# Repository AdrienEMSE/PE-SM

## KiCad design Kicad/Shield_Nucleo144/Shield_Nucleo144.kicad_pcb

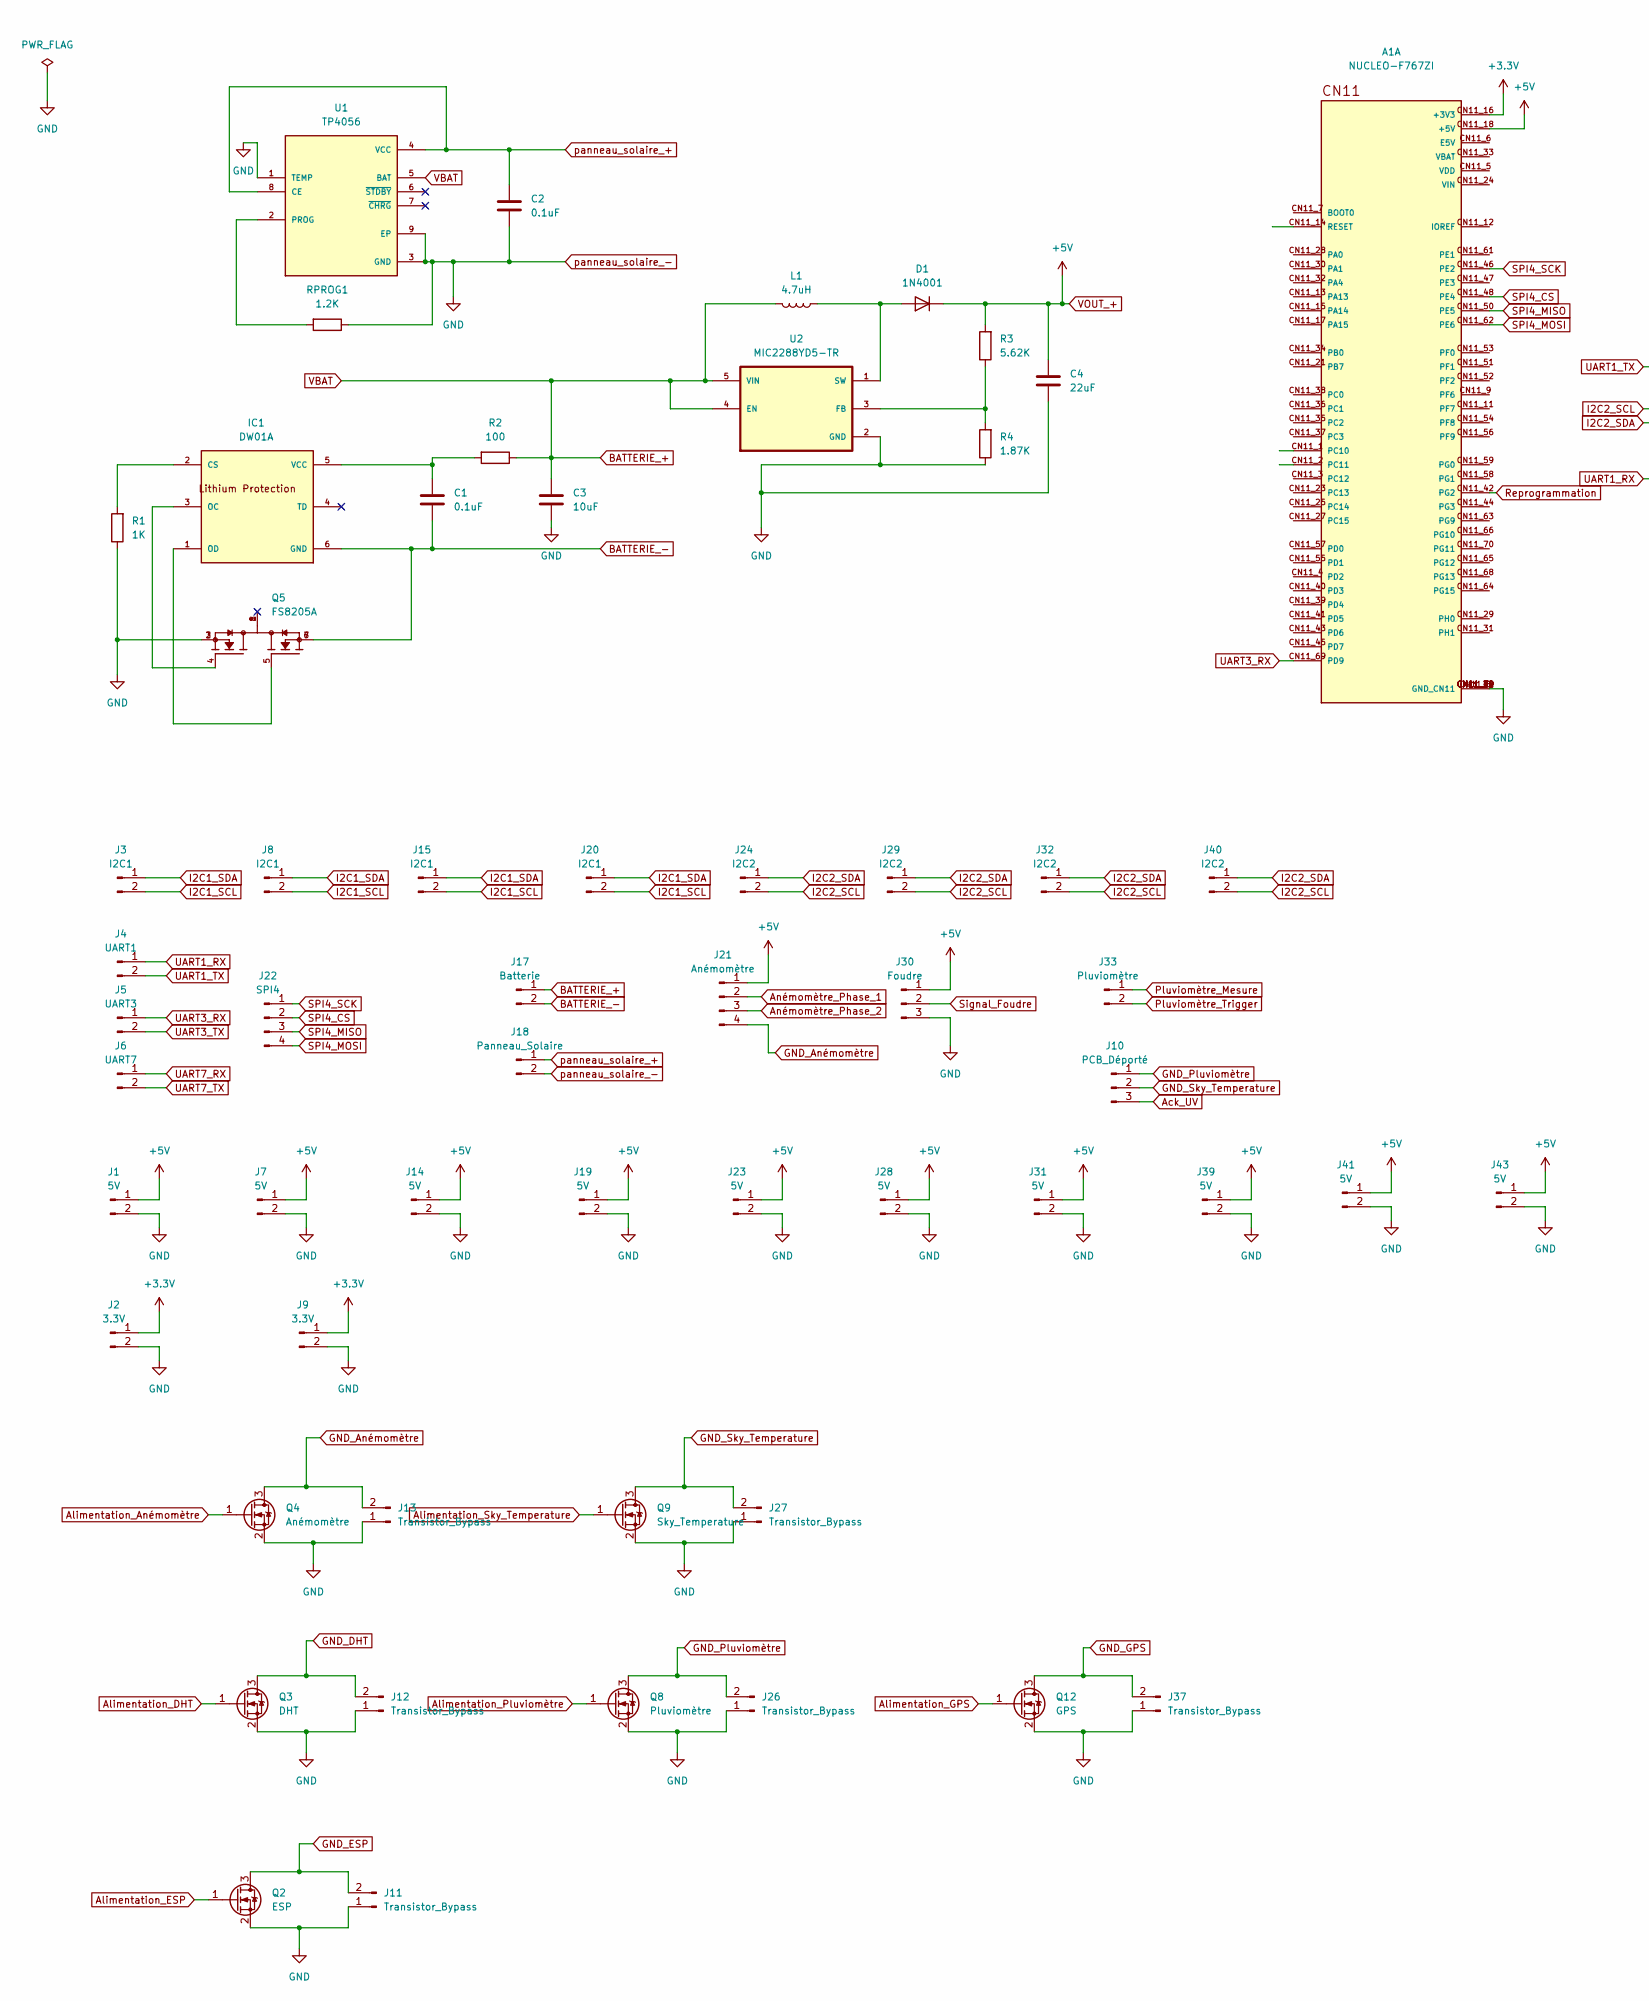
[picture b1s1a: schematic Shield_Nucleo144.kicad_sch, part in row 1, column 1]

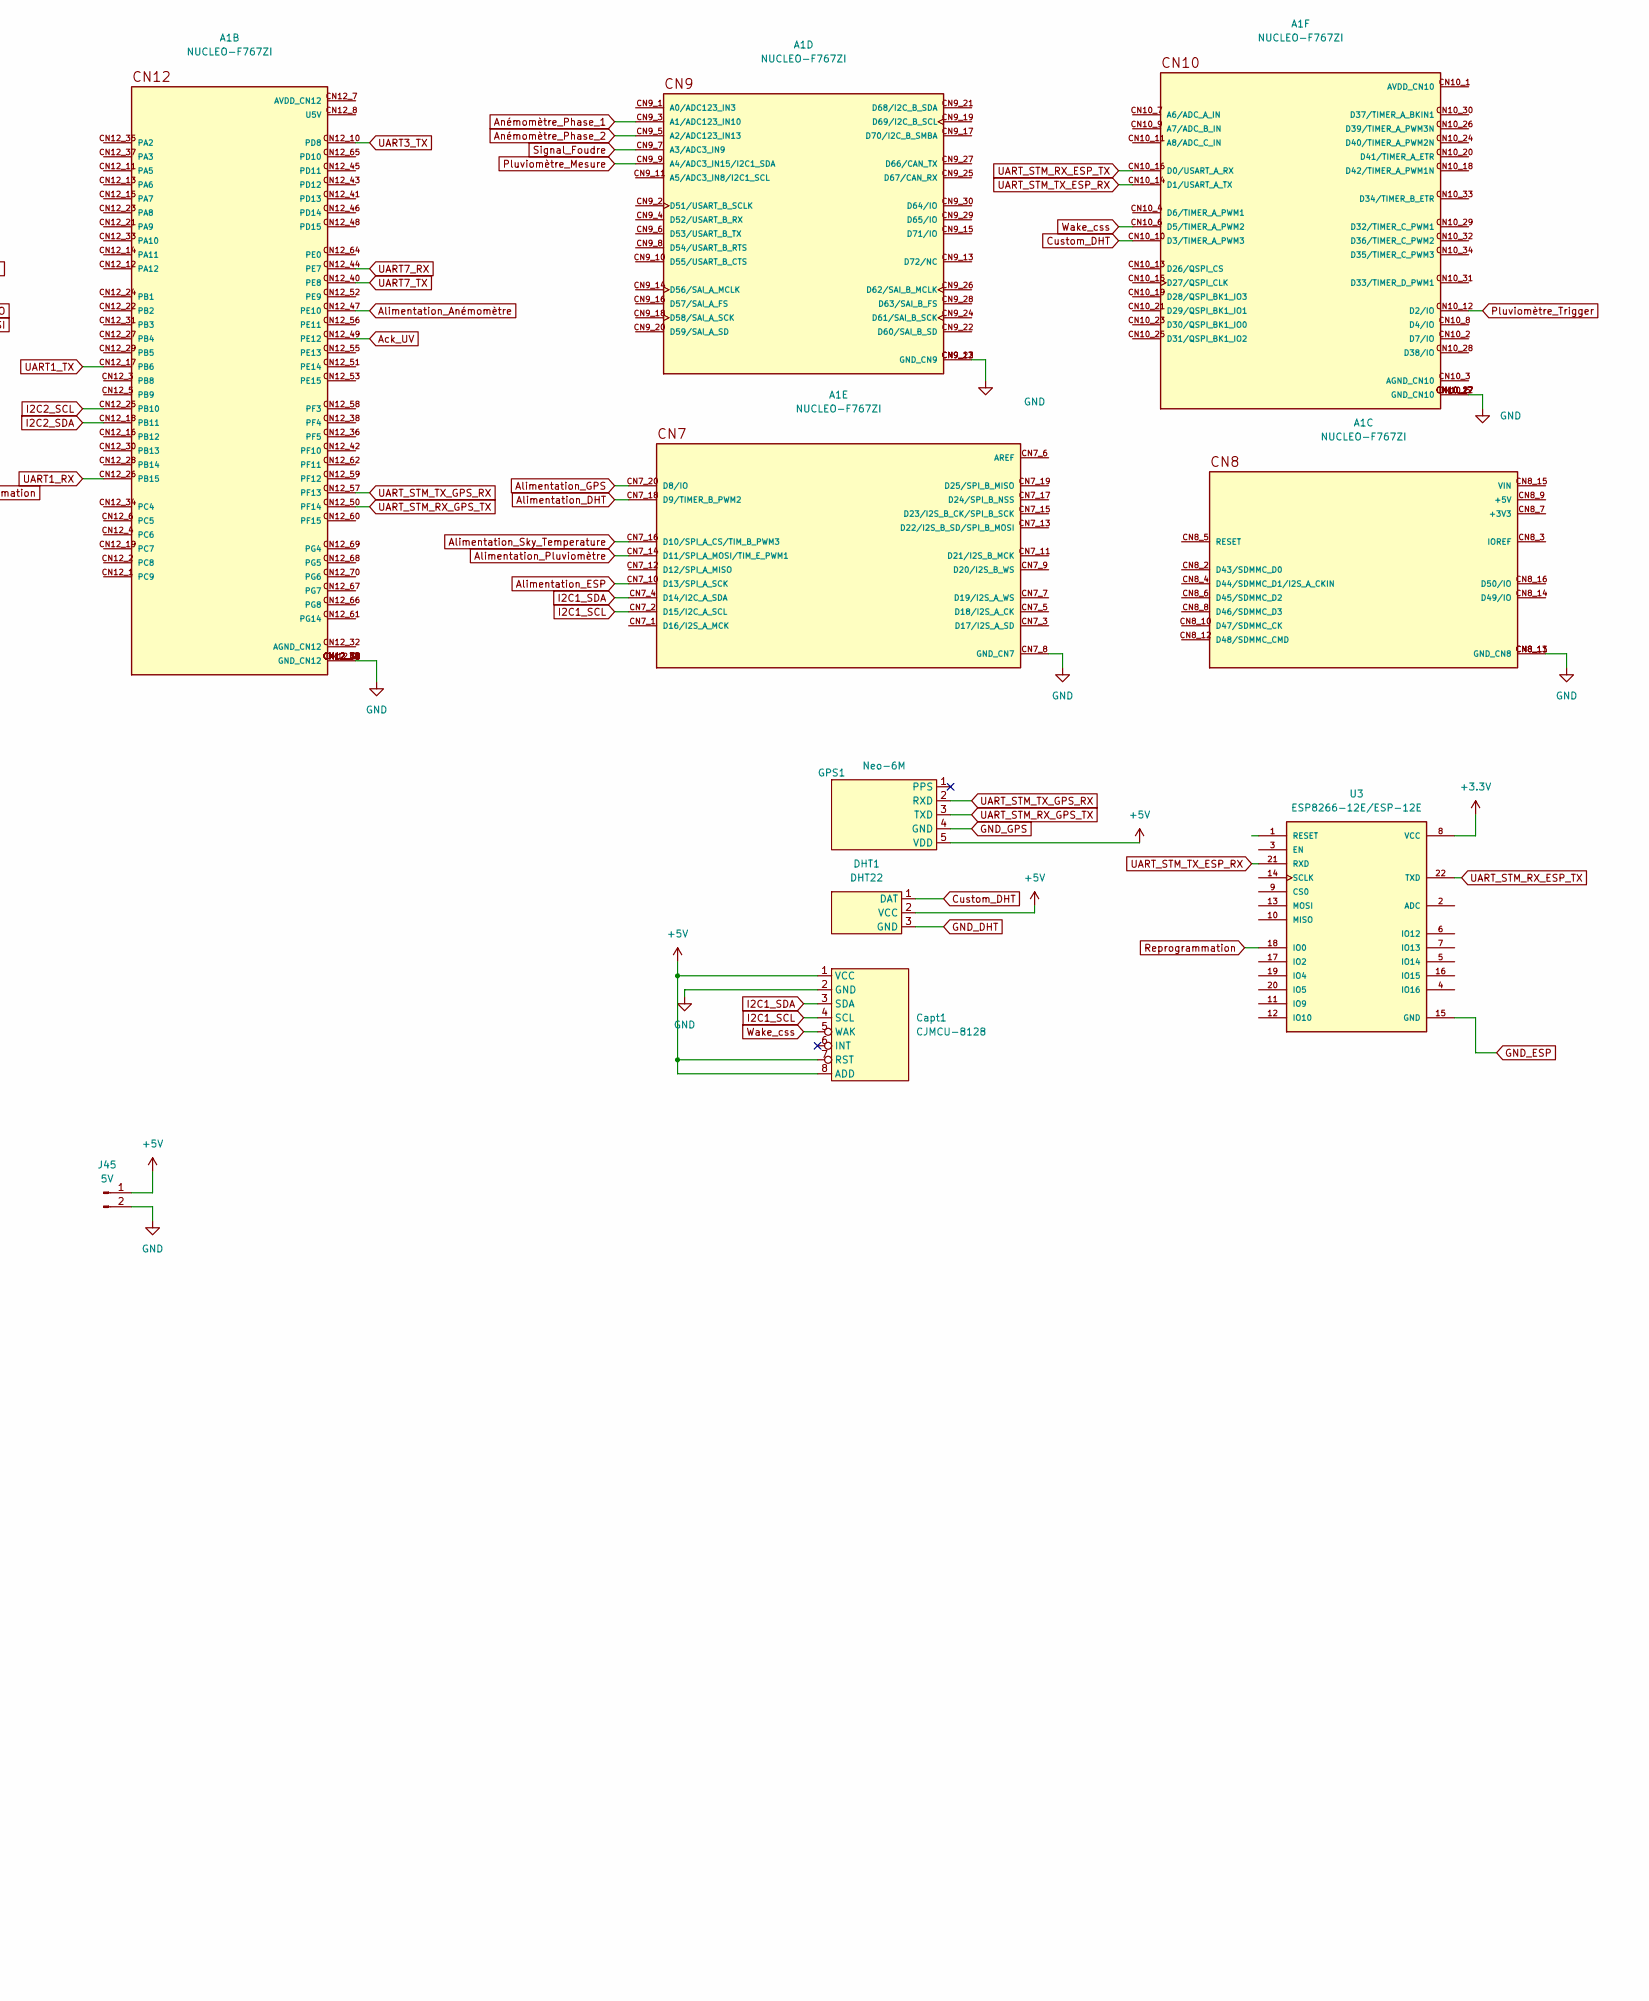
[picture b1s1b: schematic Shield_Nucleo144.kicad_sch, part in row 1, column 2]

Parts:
A1: NUCLEO-F767ZI; ST_NUCLEO-F767ZI; PARTREV 7
C1, C2: 0.1uF; C_0603_1608Metric
C3: 10uF; C_0603_1608Metric
C4: 22uF; C_0805_2012Metric
Capt1: CJMCU-8128; AQHT
D1: 1N4001; D_SOD-123
DHT1: DHT22; DHT
GPS1: Neo-6M; GPS
IC1: DW01A; SOT-23-6; MPN DW01A; LCSC C351410
J1, J7, J14, J19, J23, J28, J31, J39, J41, J43, J45: 5V; JST_EH_B2B-EH-A_1x02_P2.50mm_Vertical
J2, J9: 3.3V; JST_EH_B2B-EH-A_1x02_P2.50mm_Vertical
J3, J8, J15, J20: I2C1; JST_EH_B2B-EH-A_1x02_P2.50mm_Vertical
J4: UART1; JST_EH_B2B-EH-A_1x02_P2.50mm_Vertical
J5: UART3; JST_EH_B2B-EH-A_1x02_P2.50mm_Vertical
J6: UART7; JST_EH_B2B-EH-A_1x02_P2.50mm_Vertical
J10: PCB_Déporté; JST_EH_B3B-EH-A_1x03_P2.50mm_Vertical
J11, J12, J13, J26, J27, J37: Transistor_Bypass; PinHeader_1x02_P2.54mm_Vertical
J17: Batterie; JST_EH_B2B-EH-A_1x02_P2.50mm_Vertical
J18: Panneau_Solaire; JST_EH_B2B-EH-A_1x02_P2.50mm_Vertical
J21: Anémomètre; JST_EH_B4B-EH-A_1x04_P2.50mm_Vertical
J22: SPI4; JST_EH_B4B-EH-A_1x04_P2.50mm_Vertical
J24, J29, J32, J40: I2C2; JST_EH_B2B-EH-A_1x02_P2.50mm_Vertical
J30: Foudre; JST_EH_B3B-EH-A_1x03_P2.50mm_Vertical
J33: Pluviomètre; JST_EH_B2B-EH-A_1x02_P2.50mm_Vertical
L1: 4.7uH; L_Vishay_IHLP-2525
Q2: ESP; SOT-23
Q3: DHT; SOT-23
Q4: Anémomètre; SOT-23
Q5: FS8205A; SOP65P640X120-8N; PARTREV 1.7
Q8: Pluviomètre; SOT-23
Q9: Sky_Temperature; SOT-23
Q12: GPS; SOT-23
R1: 1K; R_0603_1608Metric
R2: 100; R_0603_1608Metric
R3: 5.62K; R_0805_2012Metric
R4: 1.87K; R_0805_2012Metric
RPROG1: 1.2K; R_0805_2012Metric
U1: TP4056; SOP127P600X175-9N
U2: MIC2288YD5-TR; TSOT-23-5; PARTREV B
U3: ESP8266-12E/ESP-12E; ESP8233

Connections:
+3.3V: A1.CN11_16 (+3V3), J2.1, J9.1, U3.8 (VCC)
Ack_UV: A1.CN12_49 (PE12), J10.3
Alimentation_Anémomètre: A1.CN12_47 (PE10), Q4.1 (G)
Alimentation_DHT: A1.CN7_18 (D9/TIMER_B_PWM2), Q3.1 (G)
Alimentation_ESP: A1.CN7_10 (D13/SPI_A_SCK), Q2.1 (G)
Alimentation_GPS: A1.CN7_20 (D8/IO), Q12.1 (G)
Alimentation_Pluviomètre: A1.CN7_14 (D11/SPI_A_MOSI/TIM_E_PWM1), Q8.1 (G)
Alimentation_Sky_Temperature: A1.CN7_16 (D10/SPI_A_CS/TIM_B_PWM3), Q9.1 (G)
Anémomètre_Phase_1: A1.CN9_3 (A1/ADC123_IN10), J21.2
Anémomètre_Phase_2: A1.CN9_5 (A2/ADC123_IN13), J21.3
BATTERIE_+: C3.1, J17.1, L1.2, R2.1, U1.5 (BAT), U2.4 (EN), U2.5 (VIN)
BATTERIE_-: C1.2, IC1.6 (GND), J17.2, Q5.6, Q5.7
Custom_DHT: A1.CN10_10 (D3/TIMER_A_PWM3), DHT1.1 (DAT)
GND_Anémomètre: J13.2, J21.4, Q4.3 (D)
GND_DHT: DHT1.3 (GND), J12.2, Q3.3 (D)
GND_ESP: J11.2, Q2.3 (D), U3.15 (GND)
GND_GPS: GPS1.4 (GND), J37.2, Q12.3 (D)
GND_Pluviomètre: J10.1, J26.2, Q8.3 (D)
GND_Sky_Temperature: J10.2, J27.2, Q9.3 (D)
I2C1_SCL: A1.CN7_2 (D15/I2C_A_SCL), Capt1.4 (SCL), J3.2, J8.2, J15.2, J20.2
I2C1_SDA: A1.CN7_4 (D14/I2C_A_SDA), Capt1.3 (SDA), J3.1, J8.1, J15.1, J20.1
I2C2_SCL: A1.CN12_25 (PB10), J24.2, J29.2, J32.2, J40.2
I2C2_SDA: A1.CN12_18 (PB11), J24.1, J29.1, J32.1, J40.1
unnamed: C1.1, IC1.5 (VCC), R2.2
unnamed: D1.2 (A), L1.1, U2.1 (SW)
unnamed: IC1.1 (OD), Q5.5
unnamed: IC1.2 (CS), R1.2
unnamed: IC1.3 (OC), Q5.4
unnamed: R3.1, R4.2, U2.3 (FB)
unnamed: RPROG1.2, U1.2 (PROG)
Pluviomètre_Mesure: A1.CN9_9 (A4/ADC3_IN15/I2C1_SDA), J33.1
Pluviomètre_Trigger: A1.CN10_12 (D2/IO), J33.2
Reprogrammation: A1.CN11_42 (PG2), U3.18 (IO0)
SPI4_CS: A1.CN11_48 (PE4), J22.2
SPI4_MISO: A1.CN11_50 (PE5), J22.3
SPI4_MOSI: A1.CN11_62 (PE6), J22.4
SPI4_SCK: A1.CN11_46 (PE2), J22.1
Signal_Foudre: A1.CN9_7 (A3/ADC3_IN9), J30.2
UART1_RX: A1.CN12_26 (PB15), J4.1
UART1_TX: A1.CN12_17 (PB6), J4.2
UART3_RX: A1.CN11_69 (PD9), J5.1
UART3_TX: A1.CN12_10 (PD8), J5.2
UART7_RX: A1.CN12_44 (PE7), J6.1
UART7_TX: A1.CN12_40 (PE8), J6.2
UART_STM_RX_ESP_TX: A1.CN10_16 (D0/USART_A_RX), U3.22 (TXD)
UART_STM_RX_GPS_TX: A1.CN12_50 (PF14), GPS1.3 (TXD)
UART_STM_TX_ESP_RX: A1.CN10_14 (D1/USART_A_TX), U3.21 (RXD)
UART_STM_TX_GPS_RX: A1.CN12_57 (PF13), GPS1.2 (RXD)
VOUT_+: A1.CN11_18 (+5V), C4.1, Capt1.1 (VCC), Capt1.7 (RST), Capt1.8 (ADD), D1.1 (K), DHT1.2 (VCC), GPS1.5 (VDD), J1.1, J7.1, J14.1, J19.1, J21.1, J23.1, J28.1, J30.1, J31.1, J39.1, J41.1, J43.1, J45.1, R3.2
Wake_css: A1.CN10_6 (D5/TIMER_A_PWM2), Capt1.5 (WAK)
panneau_solaire_+: C2.1, J18.1, U1.4 (VCC), U1.8 (CE)
panneau_solaire_-: A1.CN7_8 (GND_CN7), A1.CN8_11 (GND_CN8), A1.CN8_13 (GND_CN8), A1.CN9_12 (GND_CN9), A1.CN9_23 (GND_CN9), A1.CN10_5 (GND_CN10), A1.CN10_17 (GND_CN10), A1.CN10_22 (GND_CN10), A1.CN10_27 (GND_CN10), A1.CN11_8 (GND_CN11), A1.CN11_19 (GND_CN11), A1.CN11_20 (GND_CN11), A1.CN11_22 (GND_CN11), A1.CN11_49 (GND_CN11), A1.CN11_60 (GND_CN11), A1.CN11_71 (GND_CN11), A1.CN11_72 (GND_CN11), A1.CN12_9 (GND_CN12), A1.CN12_20 (GND_CN12), A1.CN12_39 (GND_CN12), A1.CN12_54 (GND_CN12), A1.CN12_63 (GND_CN12), A1.CN12_71 (GND_CN12), A1.CN12_72 (GND_CN12), C2.2, C3.2, C4.2, Capt1.2 (GND), J1.2, J2.2, J7.2, J9.2, J11.1, J12.1, J13.1, J14.2, J18.2, J19.2, J23.2, J26.1, J27.1, J28.2, J30.3, J31.2, J37.1, J39.2, J41.2, J43.2, J45.2, Q2.2 (S), Q3.2 (S), Q4.2 (S), Q5.2, Q5.3, Q8.2 (S), Q9.2 (S), Q12.2 (S), R1.1, R4.1, RPROG1.1, U1.1 (TEMP), U1.3 (GND), U1.9 (EP), U2.2 (GND)

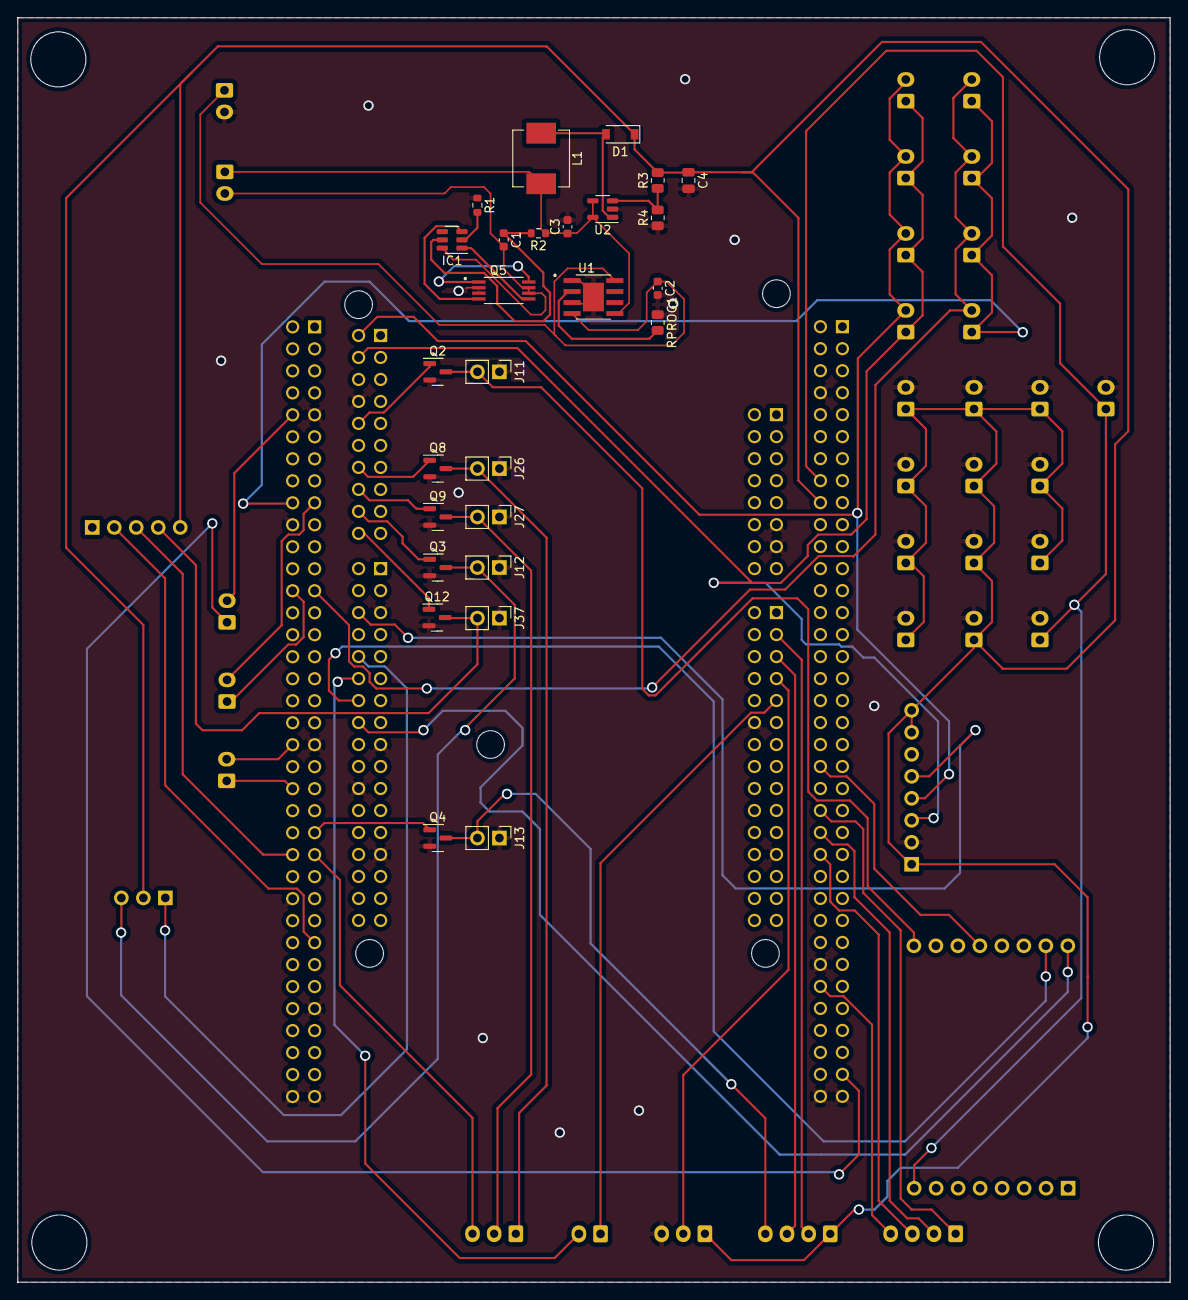
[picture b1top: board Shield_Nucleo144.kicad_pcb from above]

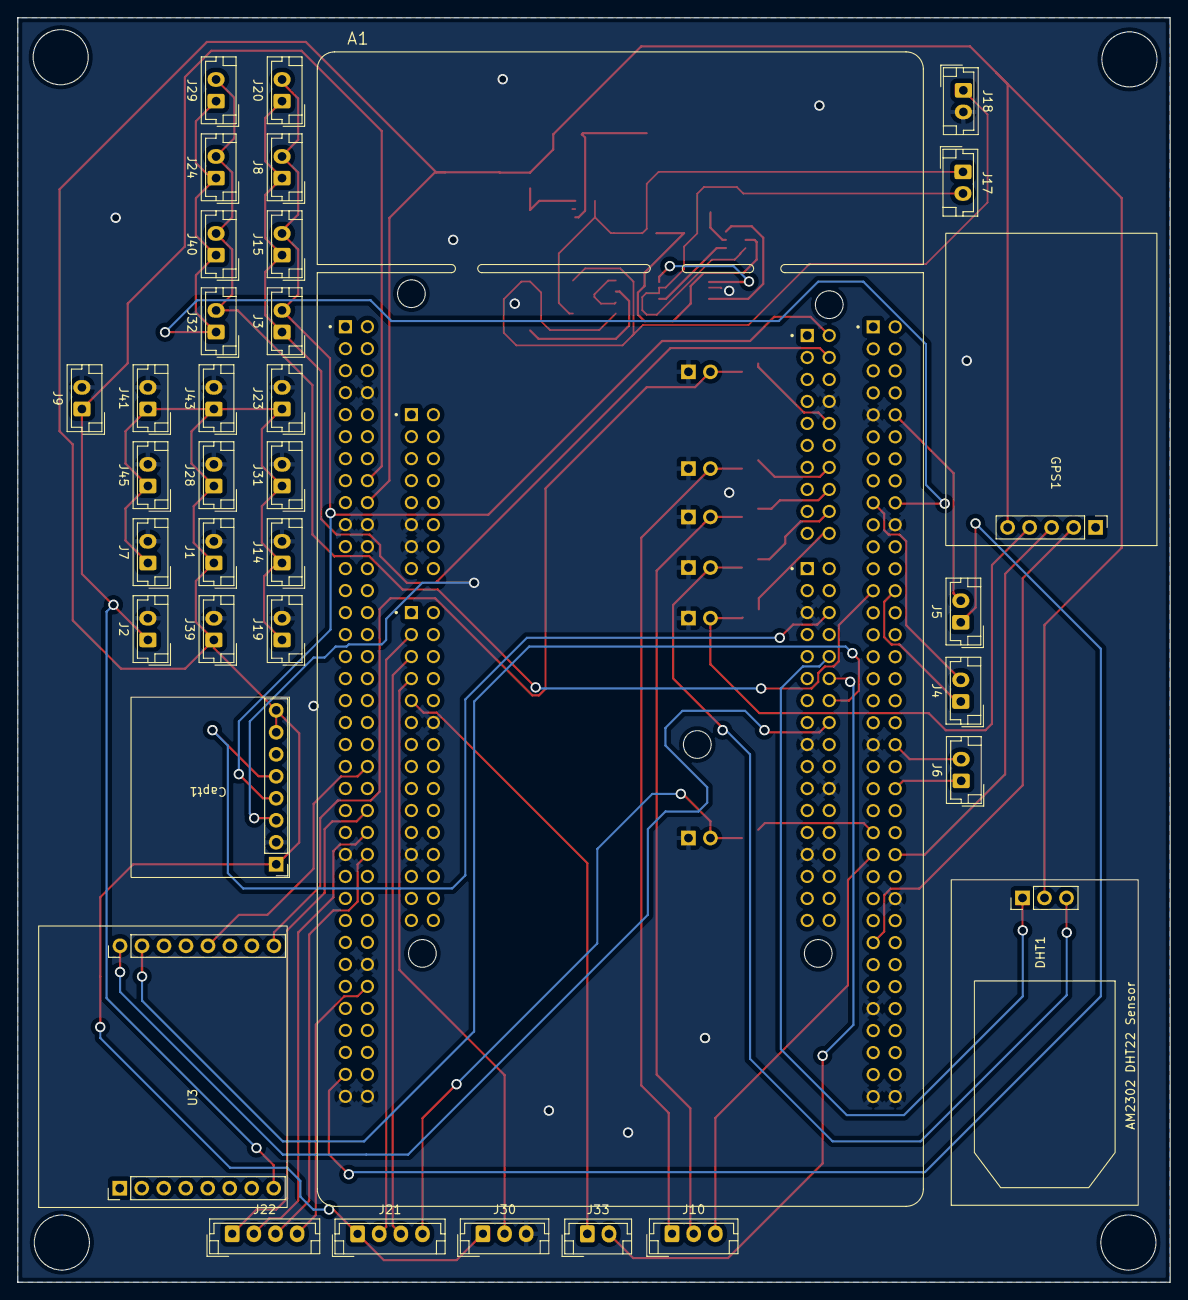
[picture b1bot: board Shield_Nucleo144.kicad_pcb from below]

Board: 2 copper layers, 133.1 x 146.0 mm, 63 parts (36 on the bottom side), 52 nets.

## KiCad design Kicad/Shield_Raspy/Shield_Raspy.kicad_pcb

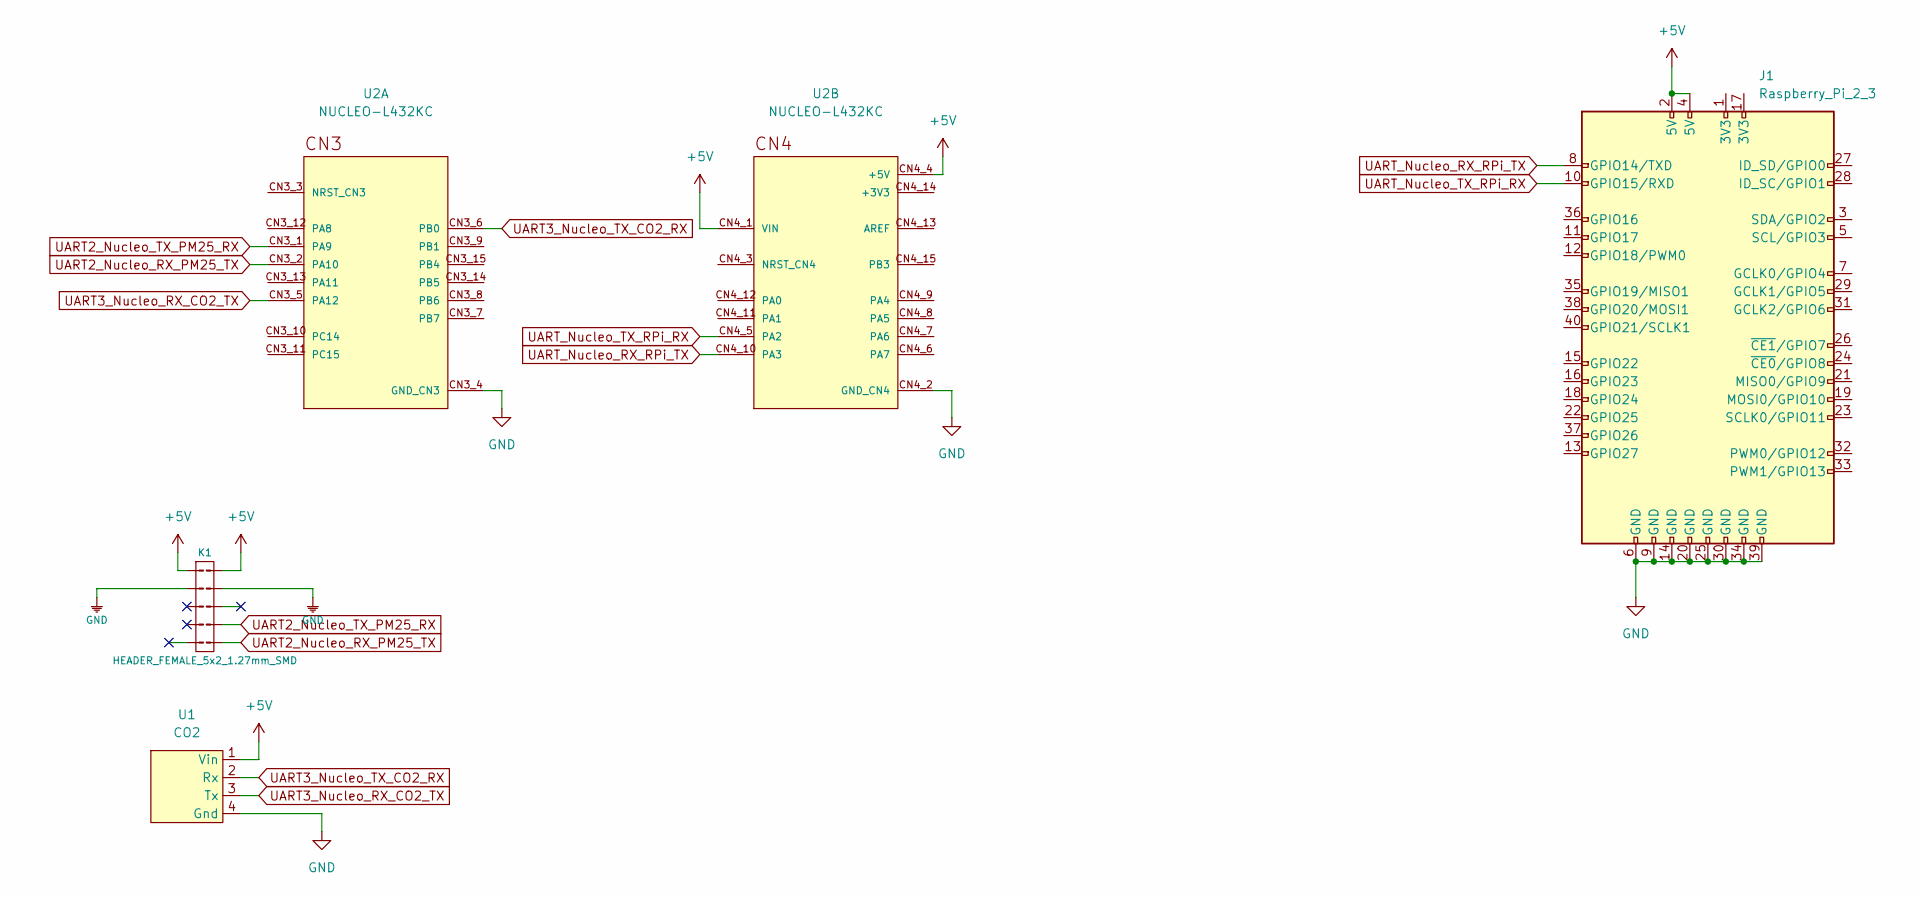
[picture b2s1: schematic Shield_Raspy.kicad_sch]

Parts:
J1: Raspberry_Pi_2_3; MODULE_RASPBERRY_PI_3_MODEL_B+
K1: HEADER_FEMALE_5x2_1.27mm_SMD; PinHeader_2x05_P1.27mm_Vertical
U1: CO2
U2: NUCLEO-L432KC; MODULE_NUCLEO-L432KC; PARTREV N/A

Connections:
+5V: J1.2 (5V), J1.4 (5V), K1.1, K1.2, U1.1 (Vin), U2.CN4_1 (VIN)
GND: J1.6 (GND), J1.9 (GND), J1.14 (GND), J1.20 (GND), J1.25 (GND), J1.30 (GND), J1.34 (GND), J1.39 (GND), K1.3, K1.4, U1.4 (Gnd), U2.CN3_4 (GND_CN3), U2.CN4_2 (GND_CN4)
UART2_Nucleo_RX_PM25_TX: K1.10, U2.CN3_2 (PA10)
UART2_Nucleo_TX_PM25_RX: K1.8, U2.CN3_1 (PA9)
UART3_Nucleo_RX_CO2_TX: U1.3 (Tx), U2.CN3_5 (PA12)
UART3_Nucleo_TX_CO2_RX: U1.2 (Rx), U2.CN3_6 (PB0)
UART_Nucleo_RX_RPi_TX: J1.8 (GPIO14/TXD), U2.CN4_10 (PA3)
UART_Nucleo_TX_RPi_RX: J1.10 (GPIO15/RXD), U2.CN4_5 (PA2)

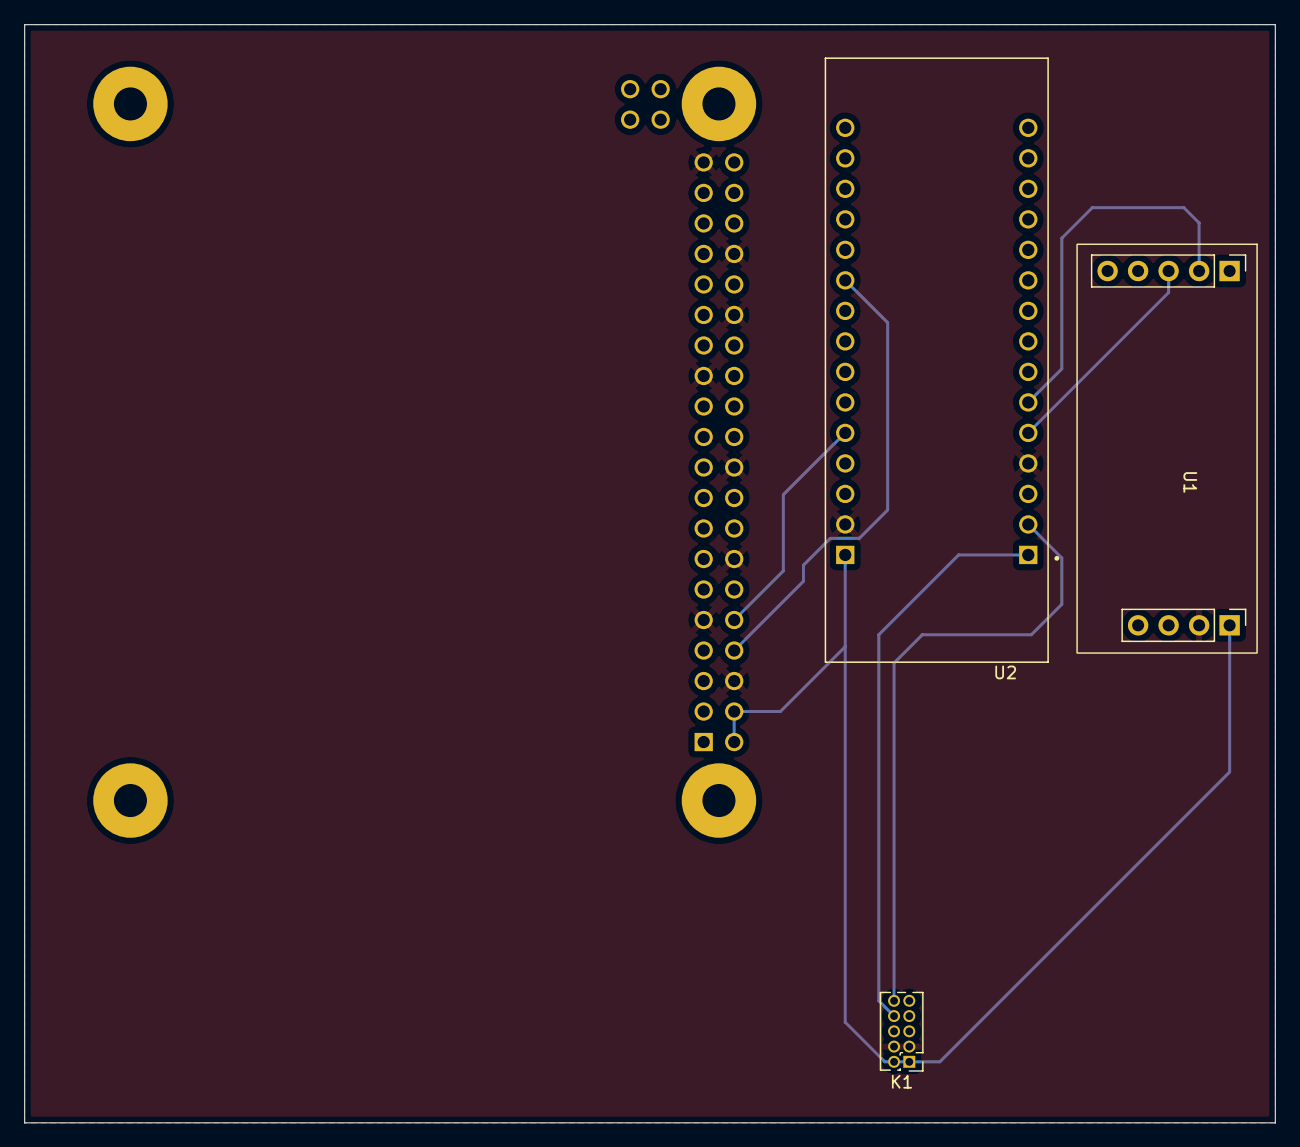
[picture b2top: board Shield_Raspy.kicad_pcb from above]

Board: 2 copper layers, 104.1 x 91.4 mm, 4 parts (1 on the bottom side), 8 nets.

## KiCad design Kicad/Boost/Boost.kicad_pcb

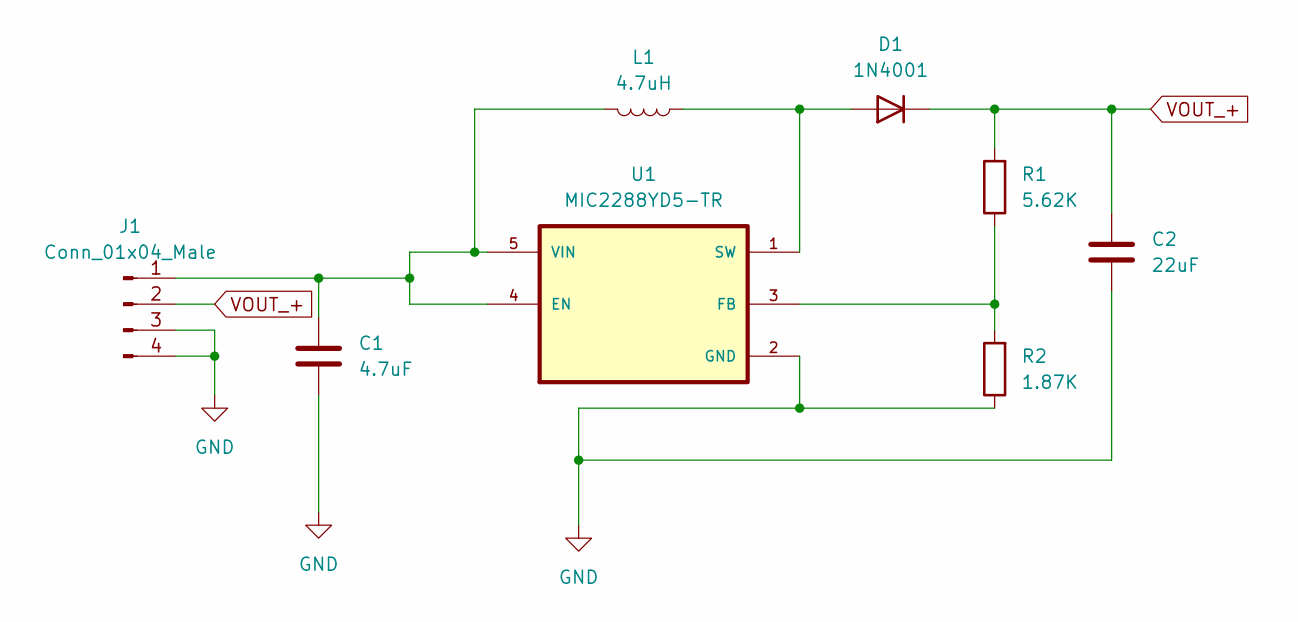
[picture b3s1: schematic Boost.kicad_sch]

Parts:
C1: 4.7uF; C_0603_1608Metric
C2: 22uF; C_0805_2012Metric
D1: 1N4001; D_SOD-123
J1: Conn_01x04_Male; PinHeader_1x04_P2.54mm_Vertical
L1: 4.7uH; L_Vishay_IHLP-2525
R1: 5.62K; R_0805_2012Metric
R2: 1.87K; R_0805_2012Metric
U1: MIC2288YD5-TR; TSOT-23-5; PARTREV B

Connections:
GND: C1.2, C2.2, J1.3, J1.4, R2.1, U1.2 (GND)
unnamed: C1.1, J1.1, L1.2, U1.4 (EN), U1.5 (VIN)
unnamed: D1.2 (A), L1.1, U1.1 (SW)
unnamed: R1.1, R2.2, U1.3 (FB)
VOUT_+: C2.1, D1.1 (K), J1.2, R1.2

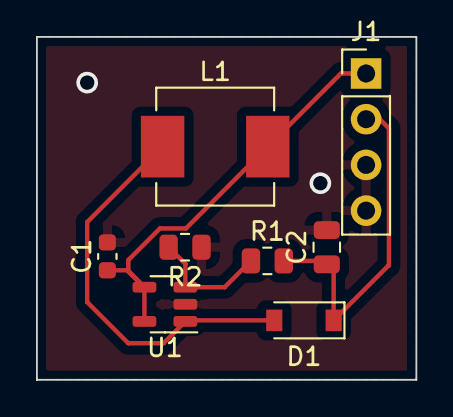
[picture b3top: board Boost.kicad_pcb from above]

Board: 2 copper layers, 21.1 x 19.0 mm, 8 parts (0 on the bottom side), 5 nets.

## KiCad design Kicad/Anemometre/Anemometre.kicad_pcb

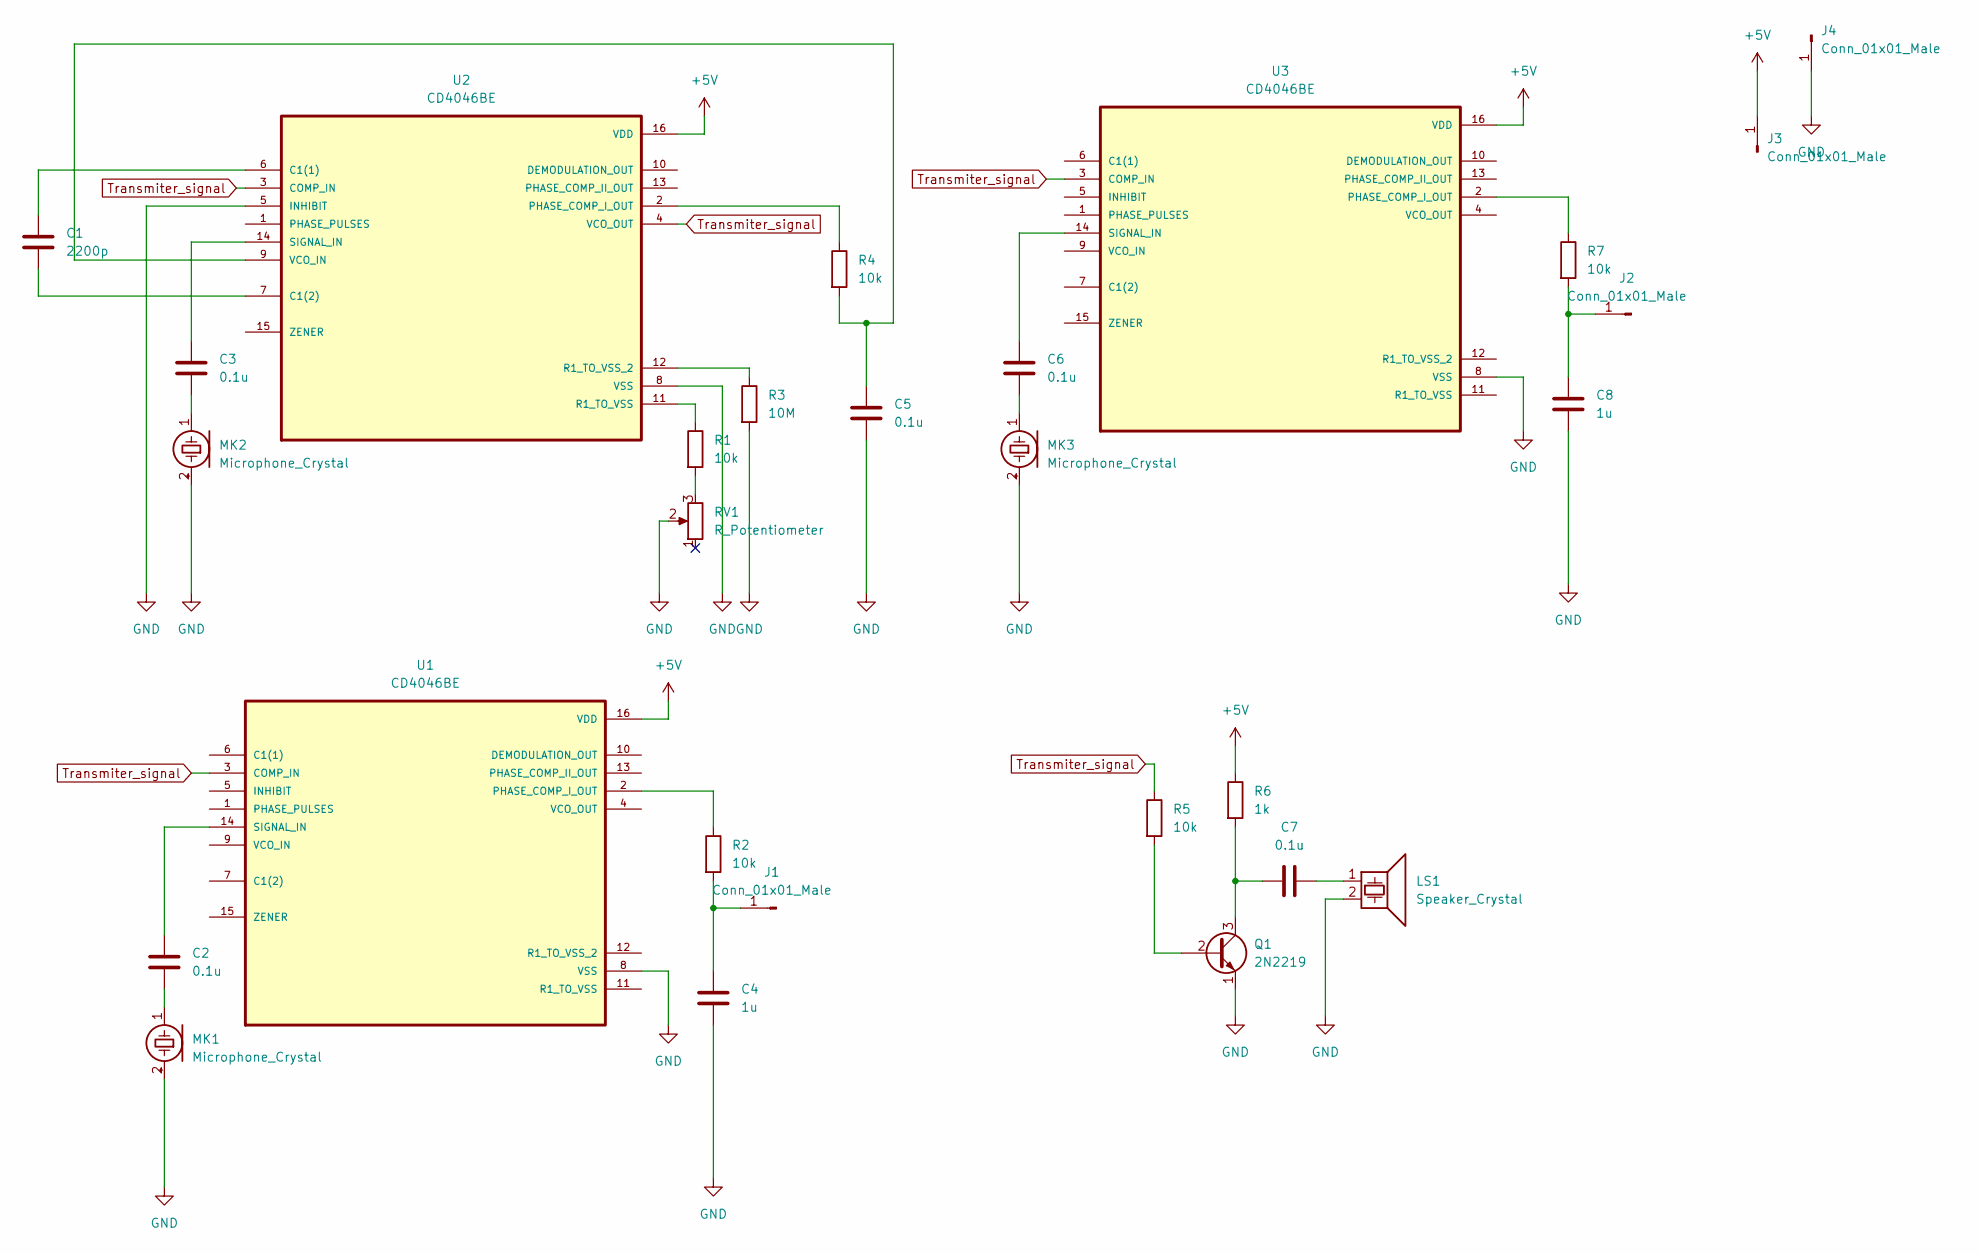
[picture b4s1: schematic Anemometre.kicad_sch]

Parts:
C1: 2200p; C_0805_2012Metric
C2, C3, C5, C6, C7: 0.1u; C_0805_2012Metric
C4, C8: 1u; C_0603_1608Metric
J1, J2, J3, J4: Conn_01x01_Male; PinHeader_1x01_P2.54mm_Vertical
LS1: Speaker_Crystal; PinHeader_1x02_P2.54mm_Vertical
MK1, MK2, MK3: Microphone_Crystal; PinHeader_1x02_P2.54mm_Vertical
Q1: 2N2219; SOT-23
R1, R2, R4, R5, R7: 10k; R_0603_1608Metric
R3: 10M; R_0603_1608Metric
R6: 1k; R_0603_1608Metric
RV1: R_Potentiometer; Potentiometer_Vishay_TS53YL_Vertical
U1, U2, U3: CD4046BE; DIP794W45P254L1969H508Q16

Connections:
+5V: J3.1, R6.1, U1.16 (VDD), U2.16 (VDD), U3.16 (VDD)
GND: C4.2, C5.2, C8.2, J4.1, LS1.2, MK1.2 (+), MK2.2 (+), MK3.2 (+), Q1.1 (E), R3.2, RV1.2, U1.8 (VSS), U2.5 (INHIBIT), U2.8 (VSS), U3.8 (VSS)
unnamed: C1.1, U2.6 (C1(1))
unnamed: C1.2, U2.7 (C1(2))
unnamed: C2.1, U1.14 (SIGNAL_IN)
unnamed: C2.2, MK1.1 (-)
unnamed: C3.1, U2.14 (SIGNAL_IN)
unnamed: C3.2, MK2.1 (-)
unnamed: C4.1, J1.1, R2.2
unnamed: C5.1, R4.2, U2.9 (VCO_IN)
unnamed: C6.1, U3.14 (SIGNAL_IN)
unnamed: C6.2, MK3.1 (-)
unnamed: C7.1, LS1.1
unnamed: C7.2, Q1.3 (C), R6.2
unnamed: C8.1, J2.1, R7.2
unnamed: Q1.2 (B), R5.2
unnamed: R1.1, U2.11 (R1_TO_VSS)
unnamed: R1.2, RV1.3
unnamed: R2.1, U1.2 (PHASE_COMP_I_OUT)
unnamed: R3.1, U2.12 (R1_TO_VSS_2)
unnamed: R4.1, U2.2 (PHASE_COMP_I_OUT)
unnamed: R7.1, U3.2 (PHASE_COMP_I_OUT)
Transmiter_signal: R5.1, U1.3 (COMP_IN), U2.3 (COMP_IN), U2.4 (VCO_OUT), U3.3 (COMP_IN)

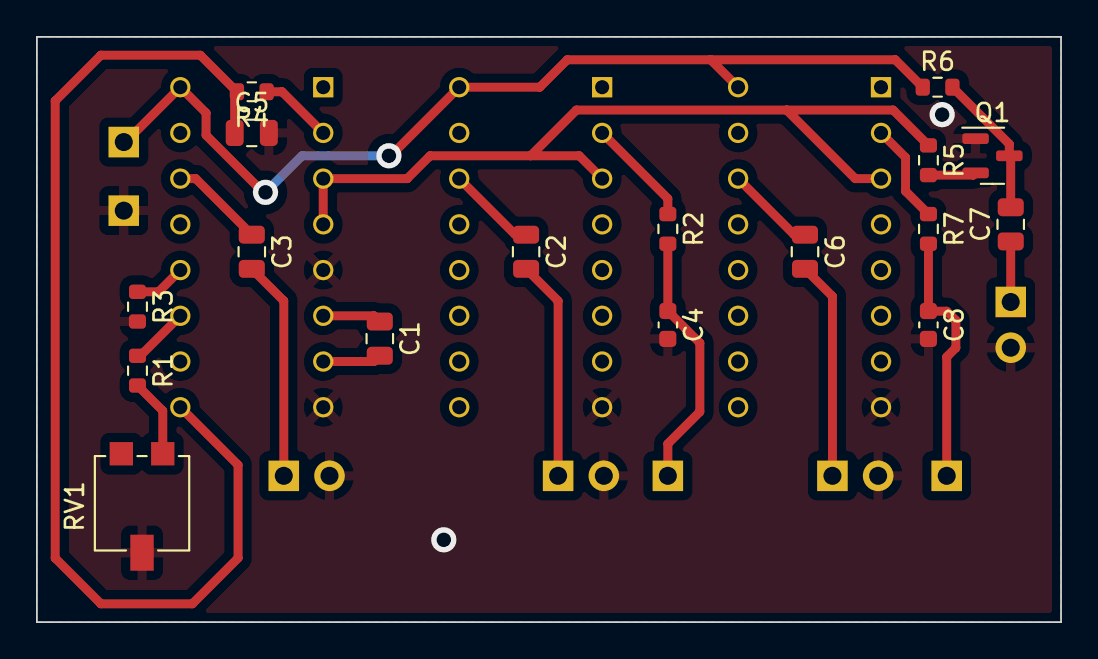
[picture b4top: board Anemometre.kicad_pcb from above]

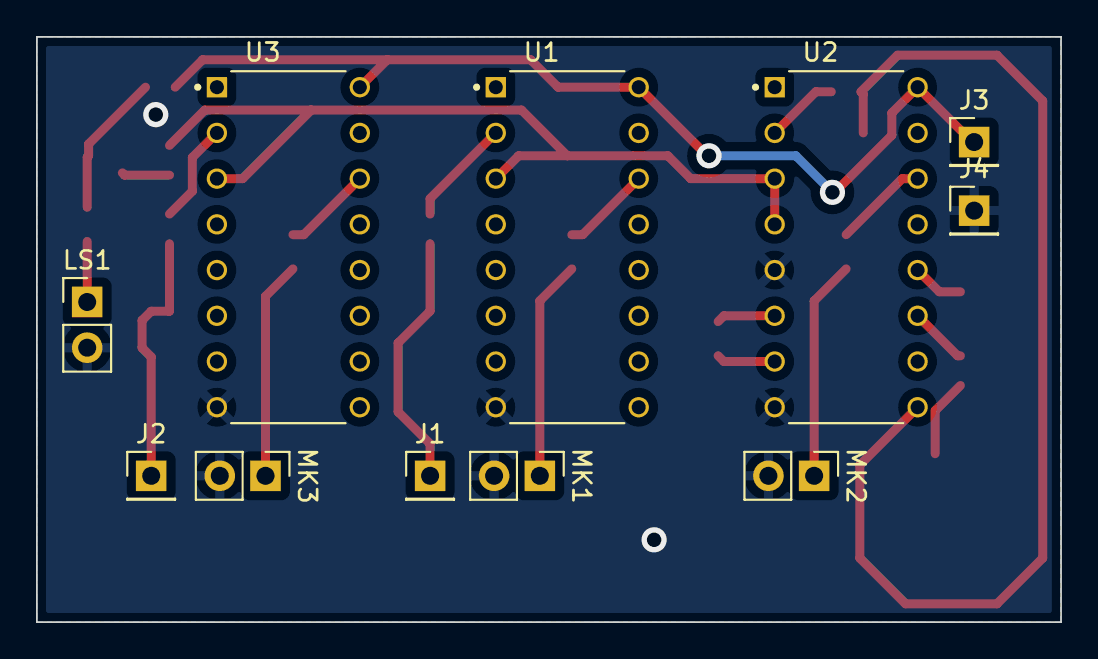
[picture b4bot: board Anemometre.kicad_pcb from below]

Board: 2 copper layers, 56.9 x 32.5 mm, 28 parts (11 on the bottom side), 23 nets.
